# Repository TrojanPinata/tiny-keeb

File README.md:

<div align="center">

# tiny keeb

### a very small keyboard

<div align="left">

**What is it?**
- This is a 60% keyboard that is 50% smaller in every direction (25% of the area) from traditional keyboard.

**What are the specs?**
- It uses [B3F-1050](https://www.digikey.com/en/products/detail/omron-electronics-inc-emc-div/B3F-1050/11889) switches and scaled down XDA keycaps on a custom PCB. The PCB links to a offboard Pi Pico running QMK.

**Why did I make this?**
- Your fingernails are bigger than the keys. No further questions.

</div>

<!--- it's so small that is's practically unusable lmao :3 -->

</div>

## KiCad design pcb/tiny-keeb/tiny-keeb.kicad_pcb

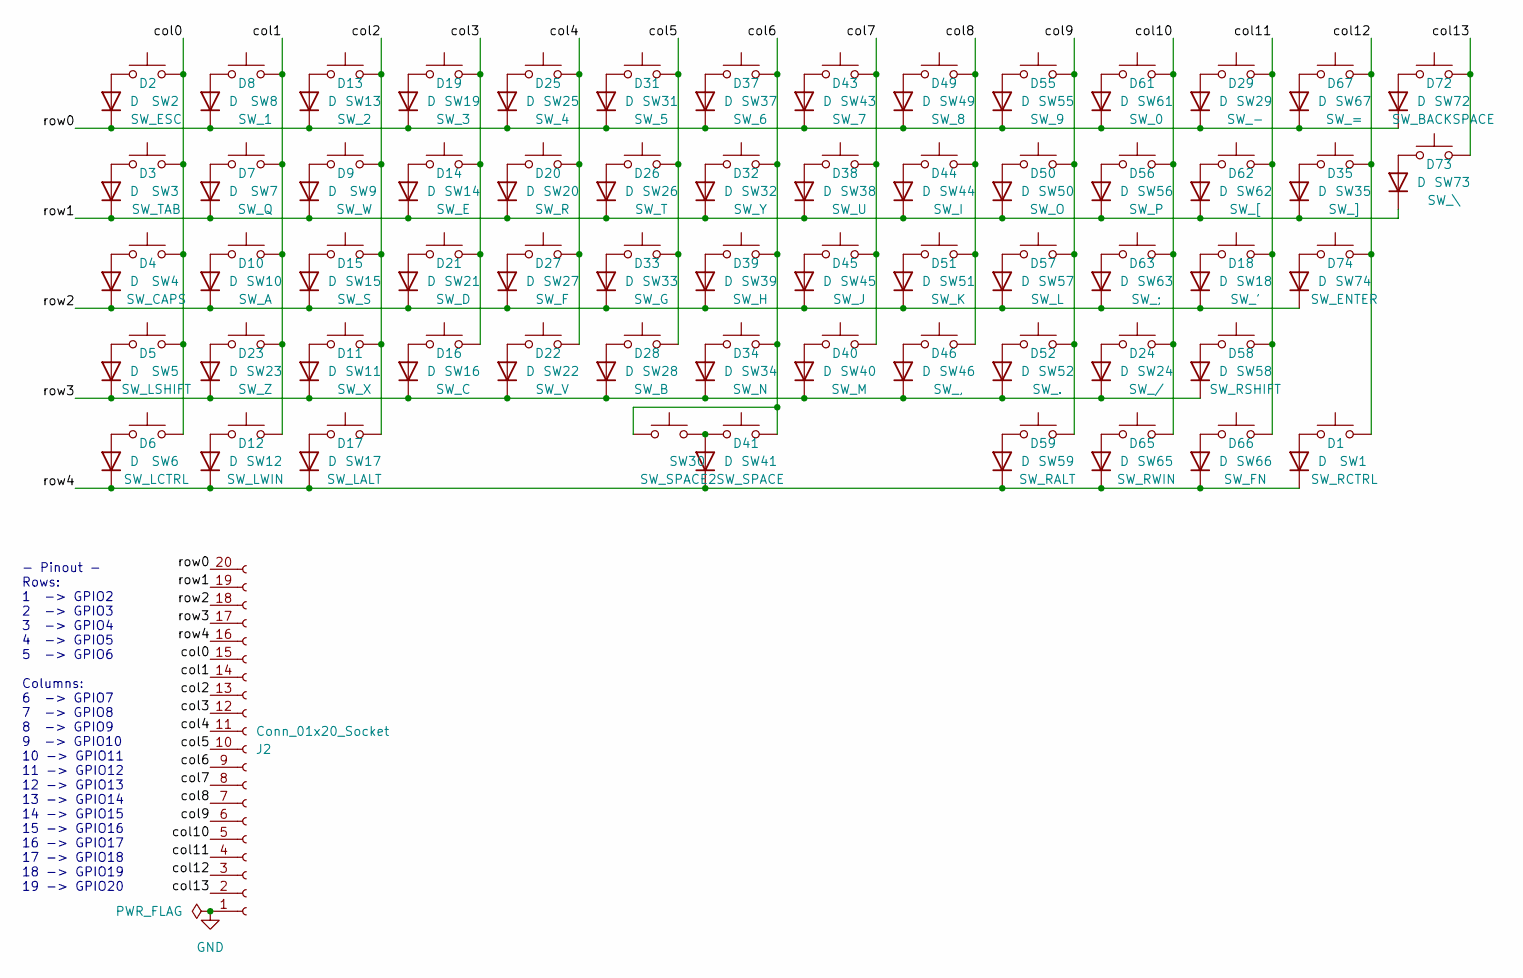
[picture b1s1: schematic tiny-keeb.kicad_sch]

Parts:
D1, D2, D3, D4, D5, D6, D7, D8, D9, D10, D11, D12, D13, D14, D15, D16, D17, D18, D19, D20, D21, D22, D23, D24, D25, D26, D27, D28, D29, D31, D32, D33, D34, D35, D37, D38, D39, D40, D41, D43, D44, D45, D46, D49, D50, D51, D52, D55, D56, D57, D58, D59, D61, D62, D63, D65, D66, D67, D72, D73, D74: D; D_SOD-123
J2: Conn_01x20_Socket; PinSocket_1x20_P2.54mm_Vertical
SW1: SW_RCTRL; SW_PUSH_6mm_square_top
SW2: SW_ESC; SW_PUSH_6mm_square_top
SW3: SW_TAB; SW_PUSH_6mm_square_top
SW4: SW_CAPS; SW_PUSH_6mm_square_top
SW5: SW_LSHIFT; SW_PUSH_6mm_square_top
SW6: SW_LCTRL; SW_PUSH_6mm_square_top
SW7: SW_Q; SW_PUSH_6mm_square_top
SW8: SW_1; SW_PUSH_6mm_square_top
SW9: SW_W; SW_PUSH_6mm_square_top
SW10: SW_A; SW_PUSH_6mm_square_top
SW11: SW_X; SW_PUSH_6mm_square_top
SW12: SW_LWIN; SW_PUSH_6mm_square_top
SW13: SW_2; SW_PUSH_6mm_square_top
SW14: SW_E; SW_PUSH_6mm_square_top
SW15: SW_S; SW_PUSH_6mm_square_top
SW16: SW_C; SW_PUSH_6mm_square_top
SW17: SW_LALT; SW_PUSH_6mm_square_top
SW18: SW_'; SW_PUSH_6mm_square_top
SW19: SW_3; SW_PUSH_6mm_square_top
SW20: SW_R; SW_PUSH_6mm_square_top
SW21: SW_D; SW_PUSH_6mm_square_top
SW22: SW_V; SW_PUSH_6mm_square_top
SW23: SW_Z; SW_PUSH_6mm_square_top
SW24: SW_/; SW_PUSH_6mm_square_top
SW25: SW_4; SW_PUSH_6mm_square_top
SW26: SW_T; SW_PUSH_6mm_square_top
SW27: SW_F; SW_PUSH_6mm_square_top
SW28: SW_B; SW_PUSH_6mm_square_top
SW29: SW_-; SW_PUSH_6mm_square_top
SW30: SW_SPACE2; SW_PUSH_6mm_square_top
SW31: SW_5; SW_PUSH_6mm_square_top
SW32: SW_Y; SW_PUSH_6mm_square_top
SW33: SW_G; SW_PUSH_6mm_square_top
SW34: SW_N; SW_PUSH_6mm_square_top
SW35: SW_]; SW_PUSH_6mm_square_top
SW37: SW_6; SW_PUSH_6mm_square_top
SW38: SW_U; SW_PUSH_6mm_square_top
SW39: SW_H; SW_PUSH_6mm_square_top
SW40: SW_M; SW_PUSH_6mm_square_top
SW41: SW_SPACE; SW_PUSH_6mm_square_top
SW43: SW_7; SW_PUSH_6mm_square_top
SW44: SW_I; SW_PUSH_6mm_square_top
SW45: SW_J; SW_PUSH_6mm_square_top
SW46: SW_,; SW_PUSH_6mm_square_top
SW49: SW_8; SW_PUSH_6mm_square_top
SW50: SW_O; SW_PUSH_6mm_square_top
SW51: SW_K; SW_PUSH_6mm_square_top
SW52: SW_.; SW_PUSH_6mm_square_top
SW55: SW_9; SW_PUSH_6mm_square_top
SW56: SW_P; SW_PUSH_6mm_square_top
SW57: SW_L; SW_PUSH_6mm_square_top
SW58: SW_RSHIFT; SW_PUSH_6mm_square_top
SW59: SW_RALT; SW_PUSH_6mm_square_top
SW61: SW_0; SW_PUSH_6mm_square_top
SW62: SW_[; SW_PUSH_6mm_square_top
SW63: SW_;; SW_PUSH_6mm_square_top
SW65: SW_RWIN; SW_PUSH_6mm_square_top
SW66: SW_FN; SW_PUSH_6mm_square_top
SW67: SW_=; SW_PUSH_6mm_square_top
SW72: SW_BACKSPACE; SW_PUSH_6mm_square_top
SW73: SW_\; SW_PUSH_6mm_square_top
SW74: SW_ENTER; SW_PUSH_6mm_square_top

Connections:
/col0: J2.15, SW2.2, SW3.2, SW4.2, SW5.2, SW6.2
/col1: J2.14, SW7.2, SW8.2, SW10.2, SW12.2, SW23.2
/col2: J2.13, SW9.2, SW11.2, SW13.2, SW15.2, SW17.2
/col3: J2.12, SW14.2, SW16.2, SW19.2, SW21.2
/col4: J2.11, SW20.2, SW22.2, SW25.2, SW27.2
/col5: J2.10, SW26.2, SW28.2, SW31.2, SW33.2
/col6: J2.9, SW30.1, SW32.2, SW34.2, SW37.2, SW39.2, SW41.2
/col7: J2.8, SW38.2, SW40.2, SW43.2, SW45.2
/col8: J2.7, SW44.2, SW46.2, SW49.2, SW51.2
/col9: J2.6, SW50.2, SW52.2, SW55.2, SW57.2, SW59.2
/col10: J2.5, SW24.2, SW56.2, SW61.2, SW63.2, SW65.2
/col11: J2.4, SW18.2, SW29.2, SW58.2, SW62.2, SW66.2
/col12: J2.3, SW1.2, SW35.2, SW67.2, SW74.2
/col13: J2.2, SW72.2, SW73.2
/row0: D2.1 (K), D8.1 (K), D13.1 (K), D19.1 (K), D25.1 (K), D29.1 (K), D31.1 (K), D37.1 (K), D43.1 (K), D49.1 (K), D55.1 (K), D61.1 (K), D67.1 (K), D72.1 (K), J2.20
/row1: D3.1 (K), D7.1 (K), D9.1 (K), D14.1 (K), D20.1 (K), D26.1 (K), D32.1 (K), D35.1 (K), D38.1 (K), D44.1 (K), D50.1 (K), D56.1 (K), D62.1 (K), D73.1 (K), J2.19
/row2: D4.1 (K), D10.1 (K), D15.1 (K), D18.1 (K), D21.1 (K), D27.1 (K), D33.1 (K), D39.1 (K), D45.1 (K), D51.1 (K), D57.1 (K), D63.1 (K), D74.1 (K), J2.18
/row3: D5.1 (K), D11.1 (K), D16.1 (K), D22.1 (K), D23.1 (K), D24.1 (K), D28.1 (K), D34.1 (K), D40.1 (K), D46.1 (K), D52.1 (K), D58.1 (K), J2.17
/row4: D1.1 (K), D6.1 (K), D12.1 (K), D17.1 (K), D41.1 (K), D59.1 (K), D65.1 (K), D66.1 (K), J2.16
GND: J2.1
unnamed: D1.2 (A), SW1.1
unnamed: D2.2 (A), SW2.1
unnamed: D3.2 (A), SW3.1
unnamed: D4.2 (A), SW4.1
unnamed: D5.2 (A), SW5.1
unnamed: D6.2 (A), SW6.1
unnamed: D7.2 (A), SW7.1
unnamed: D8.2 (A), SW8.1
unnamed: D9.2 (A), SW9.1
unnamed: D10.2 (A), SW10.1
unnamed: D11.2 (A), SW11.1
unnamed: D12.2 (A), SW12.1
unnamed: D13.2 (A), SW13.1
unnamed: D14.2 (A), SW14.1
unnamed: D15.2 (A), SW15.1
unnamed: D16.2 (A), SW16.1
unnamed: D17.2 (A), SW17.1
unnamed: D18.2 (A), SW18.1
unnamed: D19.2 (A), SW19.1
unnamed: D20.2 (A), SW20.1
unnamed: D21.2 (A), SW21.1
unnamed: D22.2 (A), SW22.1
unnamed: D23.2 (A), SW23.1
unnamed: D24.2 (A), SW24.1
unnamed: D25.2 (A), SW25.1
unnamed: D26.2 (A), SW26.1
unnamed: D27.2 (A), SW27.1
unnamed: D28.2 (A), SW28.1
unnamed: D29.2 (A), SW29.1
unnamed: D31.2 (A), SW31.1
unnamed: D32.2 (A), SW32.1
unnamed: D33.2 (A), SW33.1
unnamed: D34.2 (A), SW34.1
unnamed: D35.2 (A), SW35.1
unnamed: D37.2 (A), SW37.1
unnamed: D38.2 (A), SW38.1
unnamed: D39.2 (A), SW39.1
unnamed: D40.2 (A), SW40.1
unnamed: D41.2 (A), SW30.2, SW41.1
unnamed: D43.2 (A), SW43.1
unnamed: D44.2 (A), SW44.1
unnamed: D45.2 (A), SW45.1
unnamed: D46.2 (A), SW46.1
unnamed: D49.2 (A), SW49.1
unnamed: D50.2 (A), SW50.1
unnamed: D51.2 (A), SW51.1
unnamed: D52.2 (A), SW52.1
unnamed: D55.2 (A), SW55.1
unnamed: D56.2 (A), SW56.1
unnamed: D57.2 (A), SW57.1
unnamed: D58.2 (A), SW58.1
unnamed: D59.2 (A), SW59.1
unnamed: D61.2 (A), SW61.1
unnamed: D62.2 (A), SW62.1
unnamed: D63.2 (A), SW63.1
unnamed: D65.2 (A), SW65.1
unnamed: D66.2 (A), SW66.1
unnamed: D67.2 (A), SW67.1
unnamed: D72.2 (A), SW72.1
unnamed: D73.2 (A), SW73.1
unnamed: D74.2 (A), SW74.1

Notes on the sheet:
- Pinout - Rows: 1 -> GPIO2 2 -> GPIO3 3 -> GPIO4 4 -> GPIO5 5 -> GPIO6 Columns: 6 -> GPIO7 7 -> GPIO8 8 -> GPIO9 9 -> GPIO10 10 -> GPIO11 11 -> GPIO12 12 -> GPIO13 13 -> GPIO14 14 -> GPIO15 15 -> GPIO16 16 -> GPIO17 17 -> GPIO18 18 -> GPIO19 19 -> GPIO20

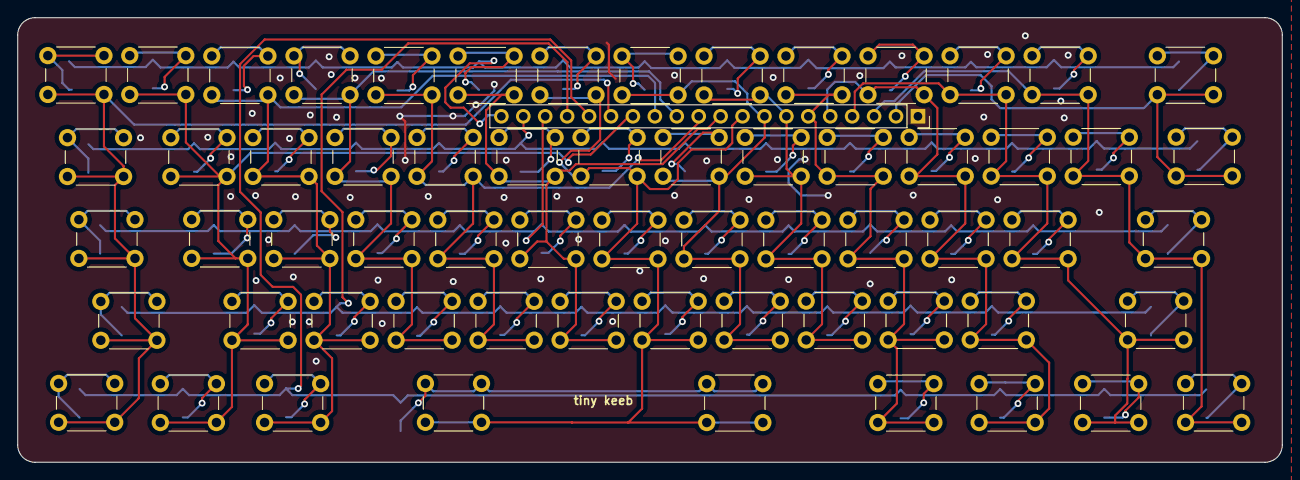
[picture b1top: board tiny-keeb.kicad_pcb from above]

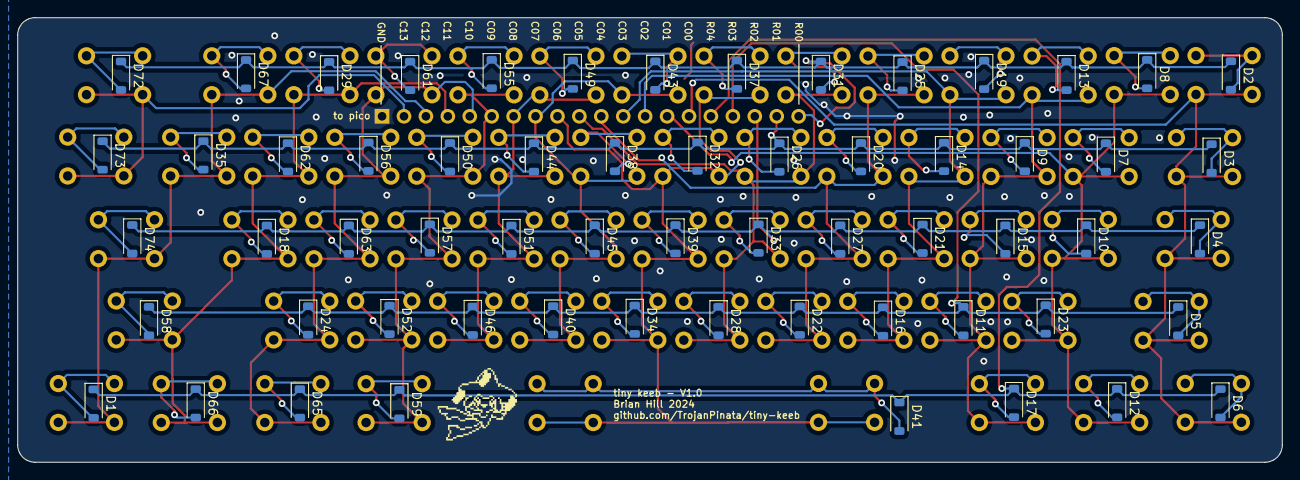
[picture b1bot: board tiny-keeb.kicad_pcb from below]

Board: 2 copper layers, 146.5 x 51.5 mm, 124 parts (61 on the bottom side), 80 nets.

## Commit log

2024-11-29 inital schematic and PCD wired, needs edge cuts, gerbers, and idea of price before go ahead
2024-12-04 pcb close to done, housing in progress, caps not started
2024-12-05 finished housing, keycaps, and pcb - waiting to order switches and pcb
2024-12-05 readme update with renders
2024-12-06 built firmware and fixed wire that was bugging me in the schematic
2024-12-07 pannelized and ordered
2024-12-20 minor fixes, first board built, add pictures later and release
2024-12-21 update readme with new pictures
